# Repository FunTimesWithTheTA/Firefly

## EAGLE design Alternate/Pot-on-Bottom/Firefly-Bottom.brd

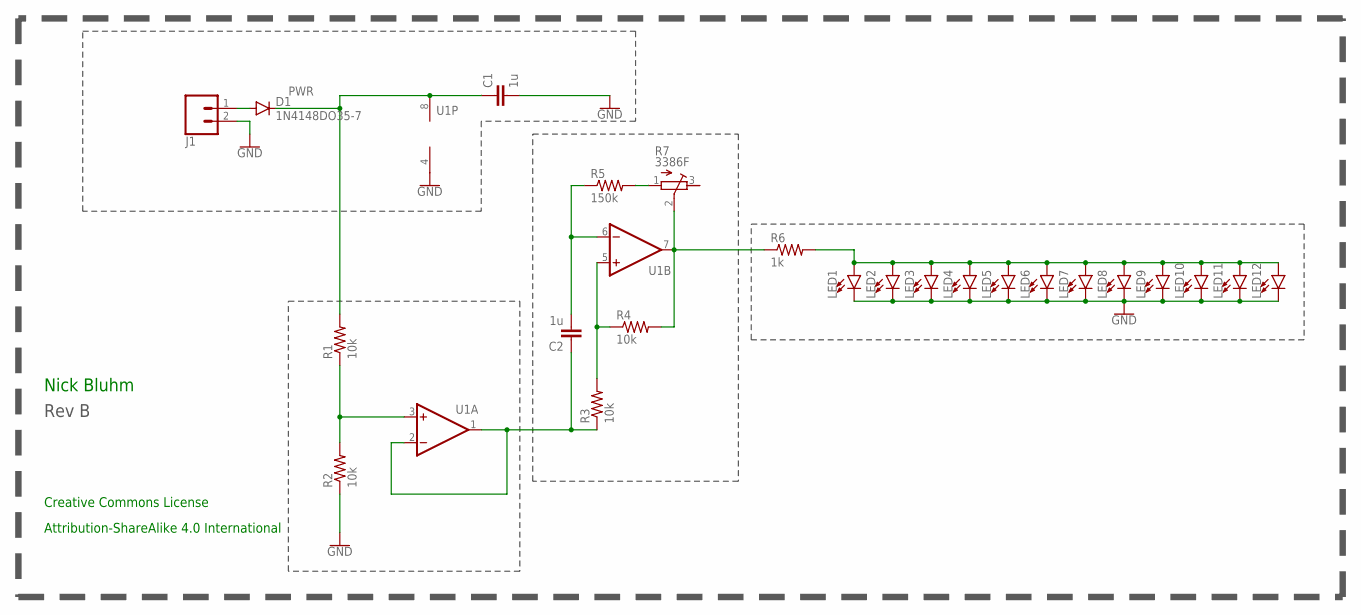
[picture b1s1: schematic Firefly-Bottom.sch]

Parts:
C1, C2: 1u; C0805
D1: 1N4148DO35-7; DO35-7
J1: CONN_02; 1X02
LED1, LED2, LED3, LED4, LED5, LED6, LED7, LED8, LED9, LED10, LED11, LED12: LED5MM; LED_5MM
R1, R2, R3, R4: 10k; R0805
R5: 150k; R0805
R6: 1k; R0805
R7: 3386F; 3386F-FOOTPRINT
U1: OP-DUALMCP6002R; SO8
U$4: REVISION.B; REV.B
U$5: LINNES.LAB.LOGO

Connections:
GND: C1.2, J1.2, LED1.K (C), LED2.K (C), LED3.K (C), LED4.K (C), LED5.K (C), LED6.K (C), LED7.K (C), LED8.K (C), LED9.K (C), LED10.K (C), LED11.K (C), LED12.K (C), R2.1, U1.4 (V-)
unnamed: D1.A, J1.1
unnamed: R1.1, R2.2, U1.3 (+IN)
unnamed: LED1.A, LED2.A, LED3.A, LED4.A, LED5.A, LED6.A, LED7.A, LED8.A, LED9.A, LED10.A, LED11.A, LED12.A, R6.2
unnamed: C2.1, R3.1, U1.1 (OUT), U1.2 (-IN)
unnamed: C2.2, R5.1, U1.6 (-IN)
unnamed: R3.2, R4.1, U1.5 (+IN)
unnamed: R4.2, R6.1, R7.2 (W), U1.7 (OUT)
unnamed: R5.2, R7.1 (A)
PWR: C1.1, D1.C, R1.2, U1.8 (V+)

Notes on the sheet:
Nick Bluhm
Creative Commons License
Attribution-ShareAlike 4.0 International

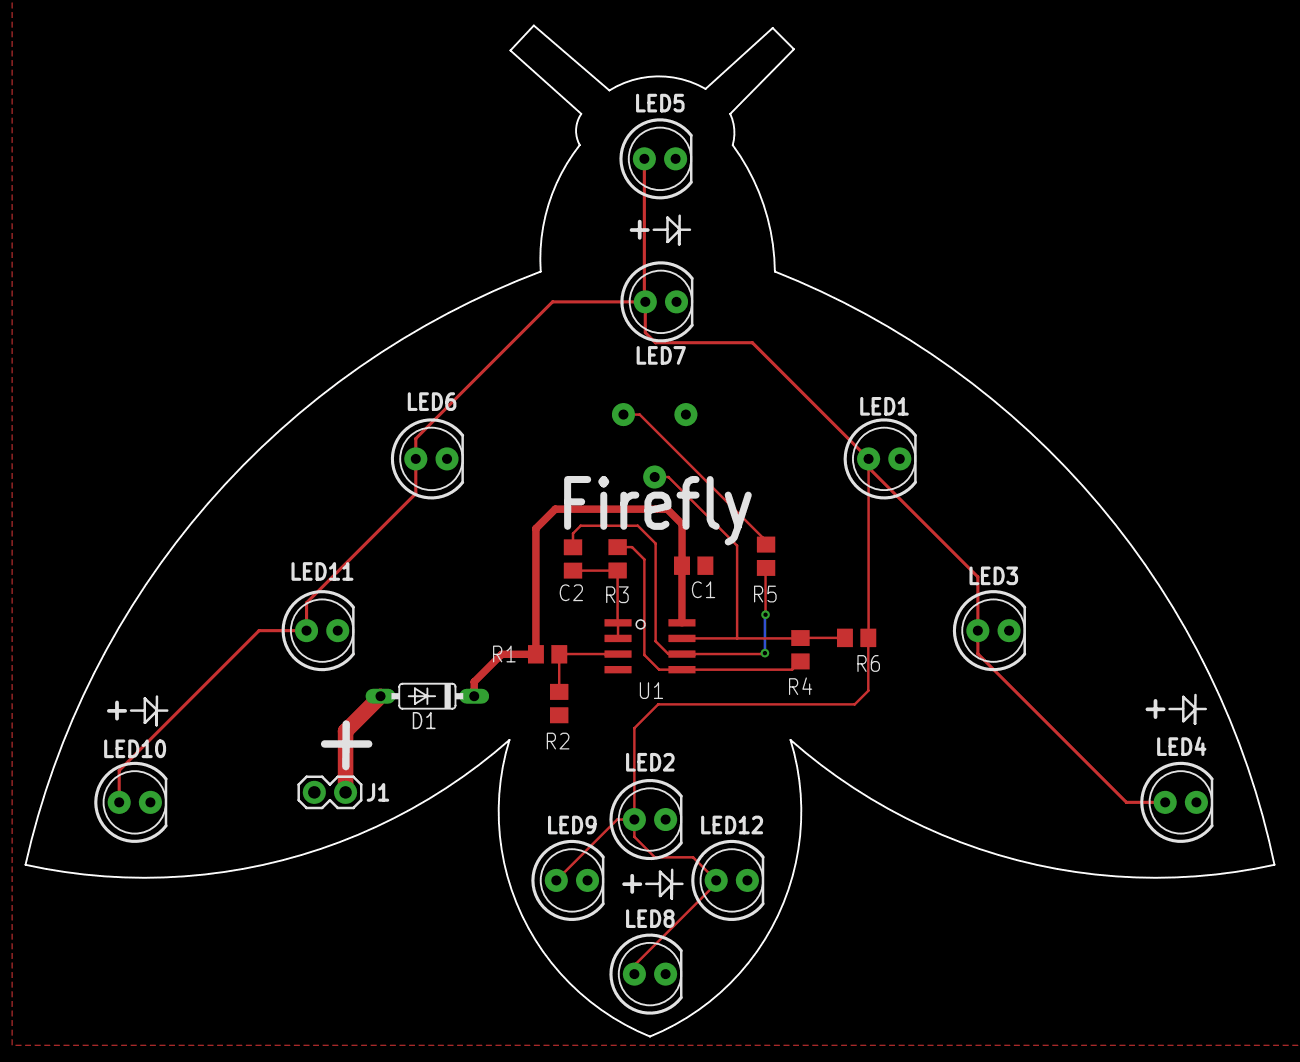
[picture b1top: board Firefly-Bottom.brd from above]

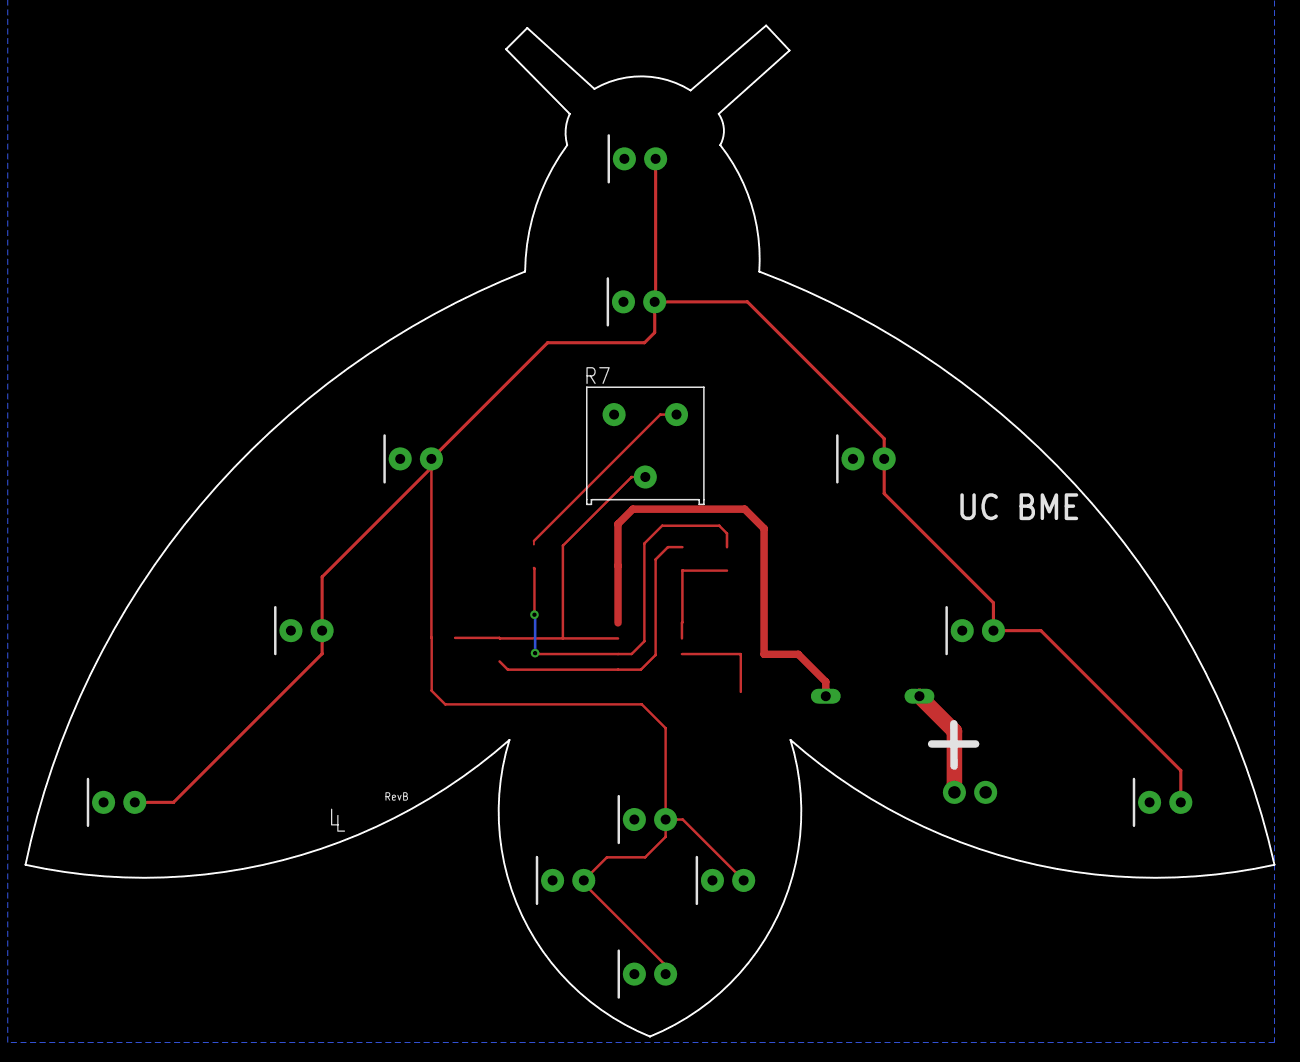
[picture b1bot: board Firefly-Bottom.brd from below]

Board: 2 copper layers, 101.6 x 82.2 mm, 26 parts (3 on the bottom side), 10 nets.

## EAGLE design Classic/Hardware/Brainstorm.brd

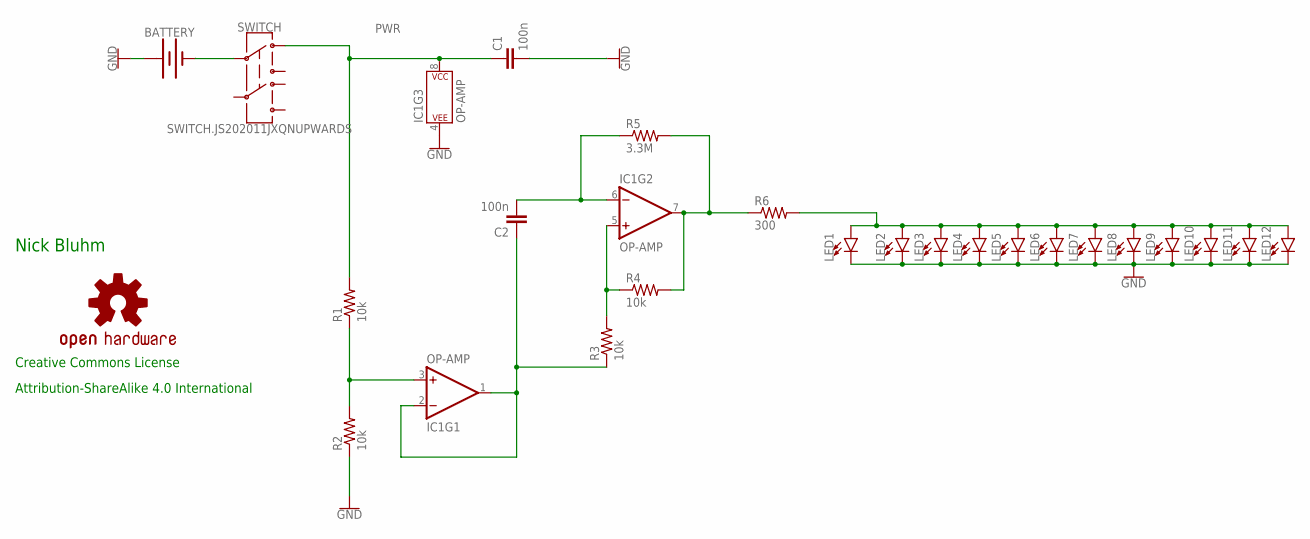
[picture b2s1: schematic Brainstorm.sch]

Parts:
BATTERY: BATTERY-20MM_SMD; BATTCON_20MM
C1, C2: 100n; C0402
IC1: OP-AMP; SO08
LED1, LED2, LED3, LED4, LED5, LED6, LED7, LED8, LED9, LED10, LED11, LED12: LED5MM; LED_5MM
LOGO1: OSHW-LOGOL-COPPER; OSHW-LOGO-L_COPPER
R1, R2, R3, R4: 10k; R0603
R5: 3.3M; R0603
R6: 300; R0603
SWITCH: SWITCH.JS202011JXQNUPWARDS; SWITCH.00
U$4: REVISION.A; REV.A
U$5: LINNES.LAB.LOGO

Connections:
GND: BATTERY.1 (+), C1.2, IC1.4 (P$V-), LED1.K (C), LED2.K (C), LED3.K (C), LED4.K (C), LED5.K (C), LED6.K (C), LED7.K (C), LED8.K (C), LED9.K (C), LED10.K (C), LED11.K (C), LED12.K (C), R2.1
unnamed: IC1.3 (+IN), R1.1, R2.2
unnamed: LED1.A, LED2.A, LED3.A, LED4.A, LED5.A, LED6.A, LED7.A, LED8.A, LED9.A, LED10.A, LED11.A, LED12.A, R6.2
unnamed: C2.1, IC1.1 (OUT), IC1.2 (-IN), R3.1
unnamed: C2.2, IC1.6 (-IN), R5.1
unnamed: IC1.5 (+IN), R3.2, R4.1
unnamed: IC1.7 (OUT), R4.2, R5.2, R6.1
unnamed: BATTERY.2 (-), SWITCH.2
PWR: C1.1, IC1.8 (P$V+), R1.2, SWITCH.1

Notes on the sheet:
Nick Bluhm
Creative Commons License
Attribution-ShareAlike 4.0 International

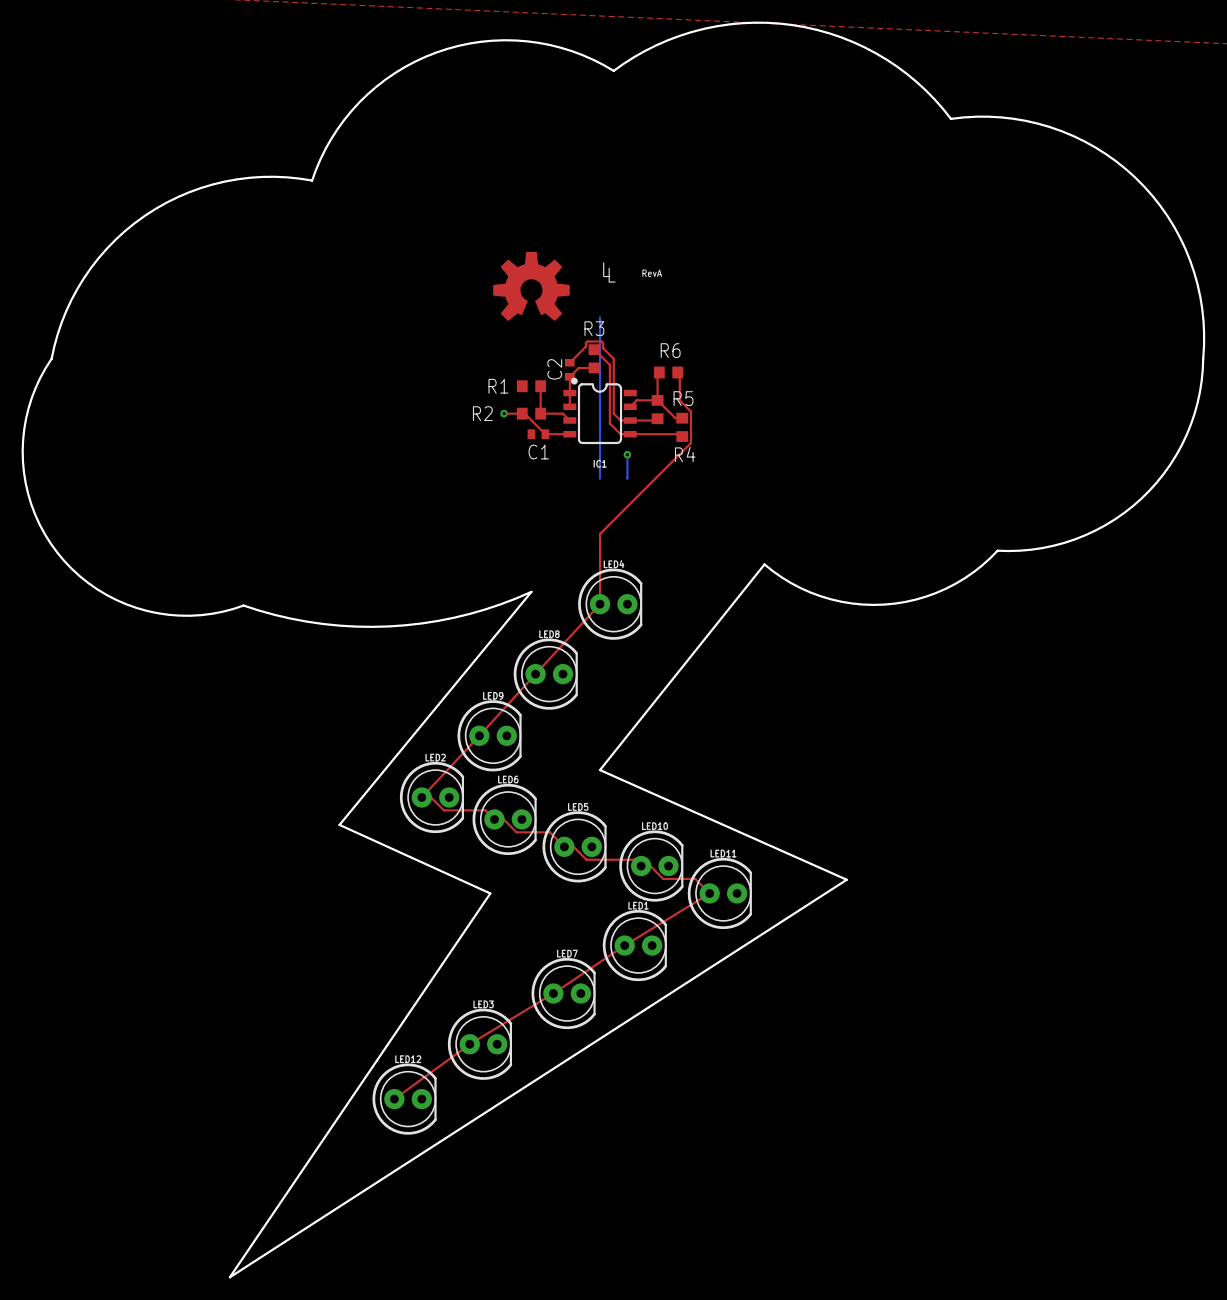
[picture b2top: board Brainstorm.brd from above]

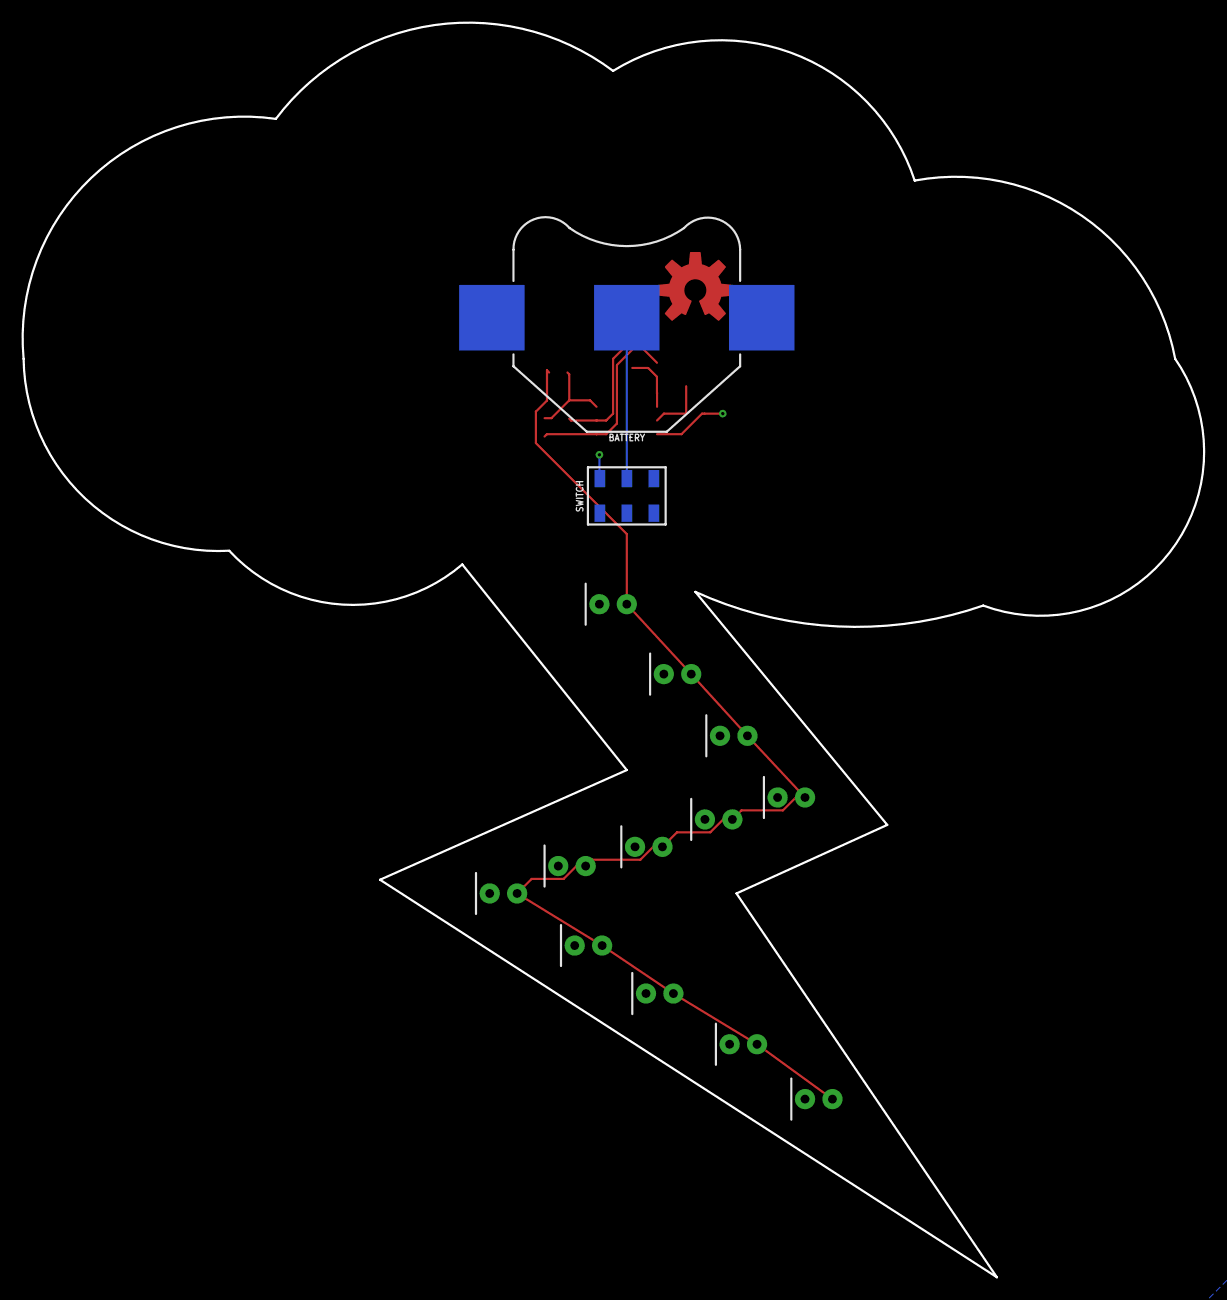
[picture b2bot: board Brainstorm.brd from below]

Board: 2 copper layers, 109.4 x 116.2 mm, 26 parts (2 on the bottom side), 9 nets.

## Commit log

2018-07-25 Adding the Firefly Eagle Files
2018-08-01 Adding the board file
2018-08-02 Adding the word doc for firefly
2018-08-02 added dash boxes and labels for subsections
2018-08-03 Adding a jpg of the 3D render of firefly
2018-08-06 updates and reorganizing things
2018-08-07 Added the Micro USB and Diodes to the board
2018-08-07 Chagned the capacitors to 0603 packages
2018-09-14 Adding the simulations for Firefly
2018-11-02 uploaded BOM and renamed hardware files
2018-11-02 added Gerber files
2019-03-29 Adding the Brainstorm files
2025-04-15 adding things before i make big changes
2025-04-15 adding everything before organizing...version with potentiometer on top and bottom is complete

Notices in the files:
parts and their libraries:
SparkFun-Batteries: Licensing: Creative Commons ShareAlike 4.0 International - https://creativecommons.org/licenses/by-sa/4.0
